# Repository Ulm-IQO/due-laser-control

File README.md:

# DUE laser control
A high resolution analog-digital digital-analog converter with PID to control
a Sirah Matisse ring laser for time resolved spectral scans.

## Hardware
An Arduino Due is used to control an AD7176 AD converter connected to 
a strain gauge measuring the laser reference cavity length and
an AD5791 DA converter that is used to drive the piezo amplifier for
the piezo that changes the reference cavity length.

We use the EVAL-AD7176-2SDZ and EVAL-AD5791SDZ reference boards with
a custom power supply (layout TBD).

A breakout board to adapt the existing RJ50 connector to SMA is also provided.

## Firmware
Right now, this can only be built with the Arduino IDE, but an addition to 
https://github.com/sudar/Arduino-Makefile is being worked on.

## Software
https://github.com/Ulm-IQO/qudi will be used to provide a user-friendly interface.

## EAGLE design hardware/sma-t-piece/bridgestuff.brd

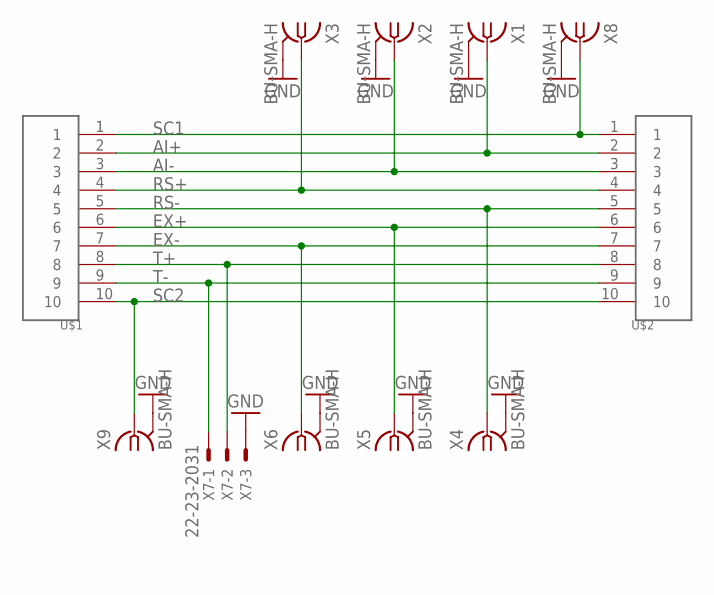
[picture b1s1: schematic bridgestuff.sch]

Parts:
U$1, U$2: RJ50-STEWARD; RJ50
X1, X2, X3, X4, X5, X6, X8, X9: BU-SMA-H
X7: 22-23-2031

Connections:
AI+: U$1.2, U$2.2, X1.1
AI-: U$1.3, U$2.3, X2.1
EX+: U$1.6, U$2.6, X5.1
EX-: U$1.7, U$2.7, X6.1
GND: X1.2, X1.3 (2), X1.4 (2), X1.5 (2), X2.2, X2.3 (2), X2.4 (2), X2.5 (2), X3.2, X3.3 (2), X3.4 (2), X3.5 (2), X4.2, X4.3 (2), X4.4 (2), X4.5 (2), X5.2, X5.3 (2), X5.4 (2), X5.5 (2), X6.2, X6.3 (2), X6.4 (2), X6.5 (2), X7.3, X8.2, X8.3 (2), X8.4 (2), X8.5 (2), X9.2, X9.3 (2), X9.4 (2), X9.5 (2)
RS+: U$1.4, U$2.4, X3.1
RS-: U$1.5, U$2.5, X4.1
SC1: U$1.1, U$2.1, X8.1
SC2: U$1.10, U$2.10, X9.1
T+: U$1.8, U$2.8, X7.2
T-: U$1.9, U$2.9, X7.1

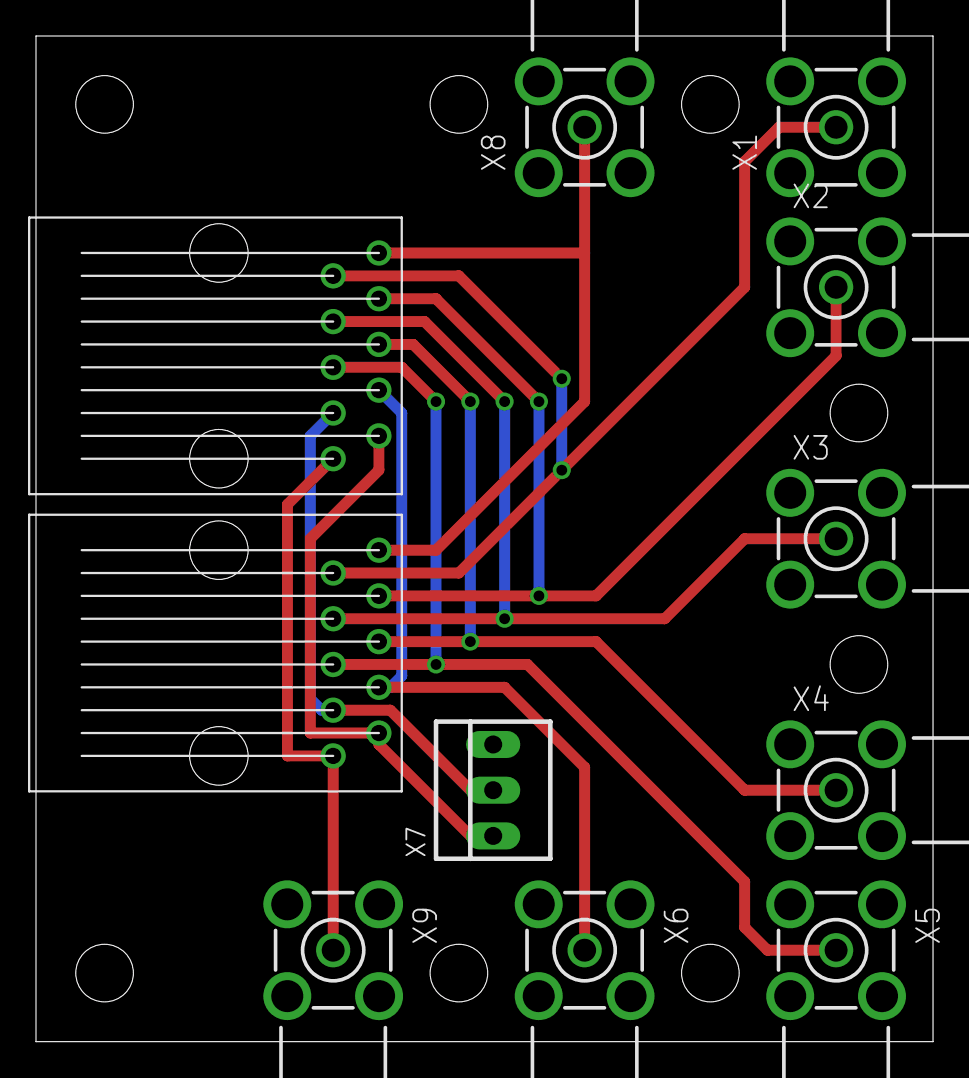
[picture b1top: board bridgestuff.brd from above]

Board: 2 copper layers, 49.8 x 55.9 mm, 11 parts (0 on the bottom side), 11 nets.

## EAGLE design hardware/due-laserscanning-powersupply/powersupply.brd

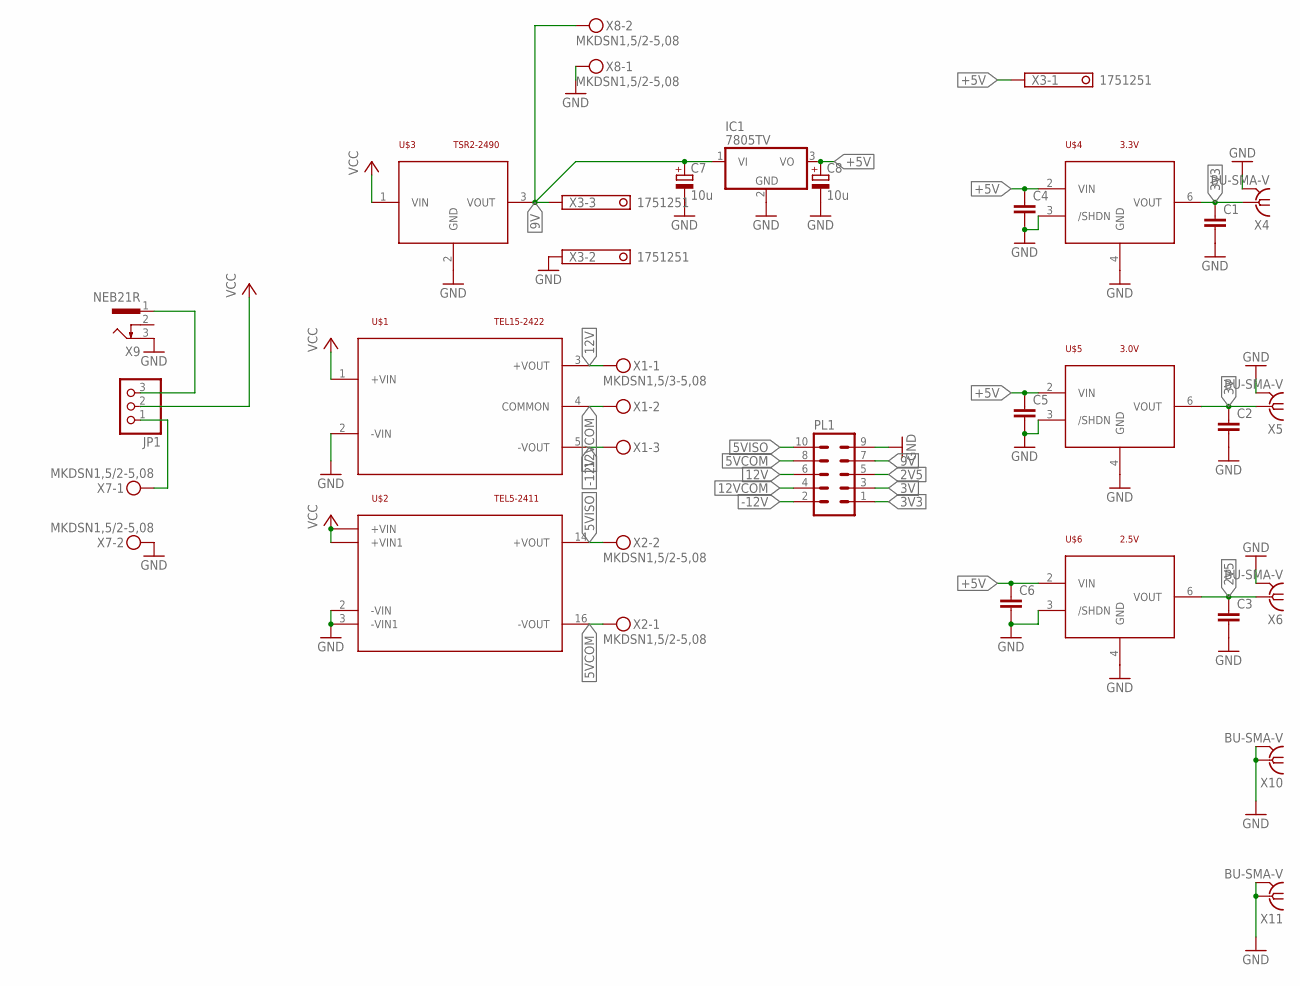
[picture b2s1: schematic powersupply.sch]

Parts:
C1, C2, C3, C4, C5, C6: C-EUC0805; C0805
C7, C8: 10u; PANASONIC_B
IC1: 7805TV; TO220V
JP1: PINHD-1X3; 1X03
PL1: 10V
U$1: TEL15-2422; TEL-15
U$2: TEL5-2411; TEL-5-SINGLE
U$3: TSR2-2490; TSR2
U$4: 3.3V; SO8
U$5: 3.0V; SO8
U$6: 2.5V; SO8
X1: MKDSN1,5/3-5,08
X2, X7, X8: MKDSN1,5/2-5,08
X3: 1751251
X4, X5, X6, X10, X11: BU-SMA-V
X9: NEB21R

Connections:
2V5: C3.1, PL1.5, U$6.6 (VOUT), X6.1
3V: C2.1, PL1.3, U$5.6 (VOUT), X5.1
3V3: C1.1, PL1.1, U$4.6 (VOUT), X4.1
5VCOM: PL1.8, U$2.16 (-VOUT), X2.1
5VISO: PL1.10, U$2.14 (+VOUT), X2.2
9V: C7.+, IC1.1 (VI), PL1.7, U$3.3 (VOUT), X3.3, X8.2
12V: PL1.6, U$1.3 (+VOUT), X1.1
12VCOM: PL1.4, U$1.4 (COMMON), X1.2
+5V: C4.1, C5.1, C6.1, C8.+, IC1.3 (VO), U$4.2 (VIN), U$5.2 (VIN), U$6.2 (VIN), X3.1
-12V: PL1.2, U$1.5 (-VOUT), X1.3
GND: C1.2, C2.2, C3.2, C4.2, C5.2, C6.2, C7.-, C8.-, IC1.2 (GND), PL1.9, U$1.2 (-VIN), U$2.2 (-VIN), U$2.3 (-VIN1), U$3.2 (GND), U$4.3 (/SHDN), U$4.4 (GND), U$5.3 (/SHDN), U$5.4 (GND), U$6.3 (/SHDN), U$6.4 (GND), X3.2, X4.2, X4.3 (2), X4.4 (2), X4.5 (2), X5.2, X5.3 (2), X5.4 (2), X5.5 (2), X6.2, X6.3 (2), X6.4 (2), X6.5 (2), X7.2, X8.1, X9.3, X10.1, X10.2, X10.3 (2), X10.4 (2), X10.5 (2), X11.1, X11.2, X11.3 (2), X11.4 (2), X11.5 (2)
unnamed: JP1.1, X7.1
unnamed: JP1.3, X9.1
VCC: JP1.2, U$1.1 (+VIN), U$2.22 (+VIN), U$2.23 (+VIN1), U$3.1 (VIN)

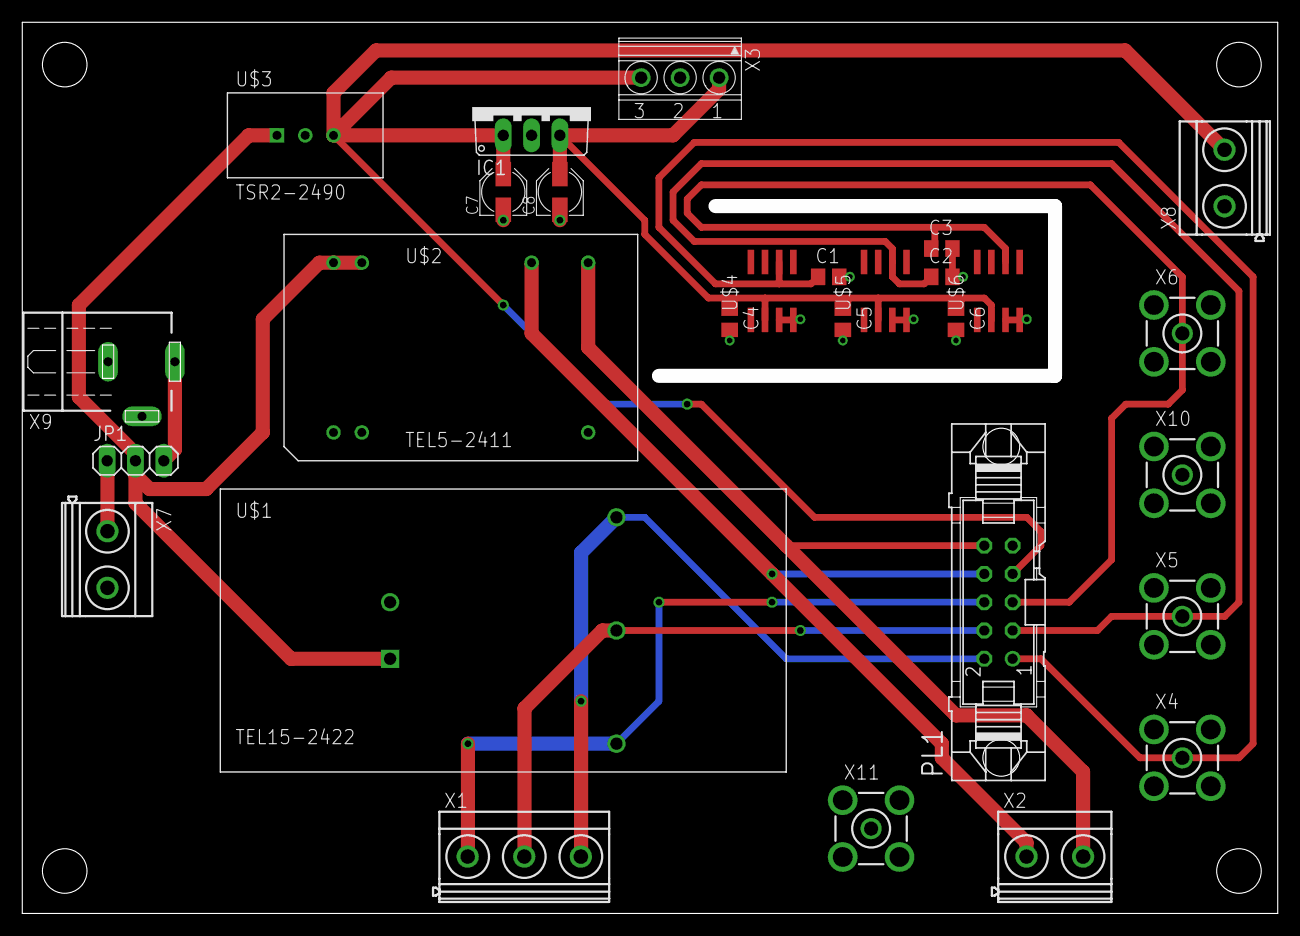
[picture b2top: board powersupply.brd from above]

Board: 2 copper layers, 111.4 x 78.7 mm, 28 parts (0 on the bottom side), 14 nets.

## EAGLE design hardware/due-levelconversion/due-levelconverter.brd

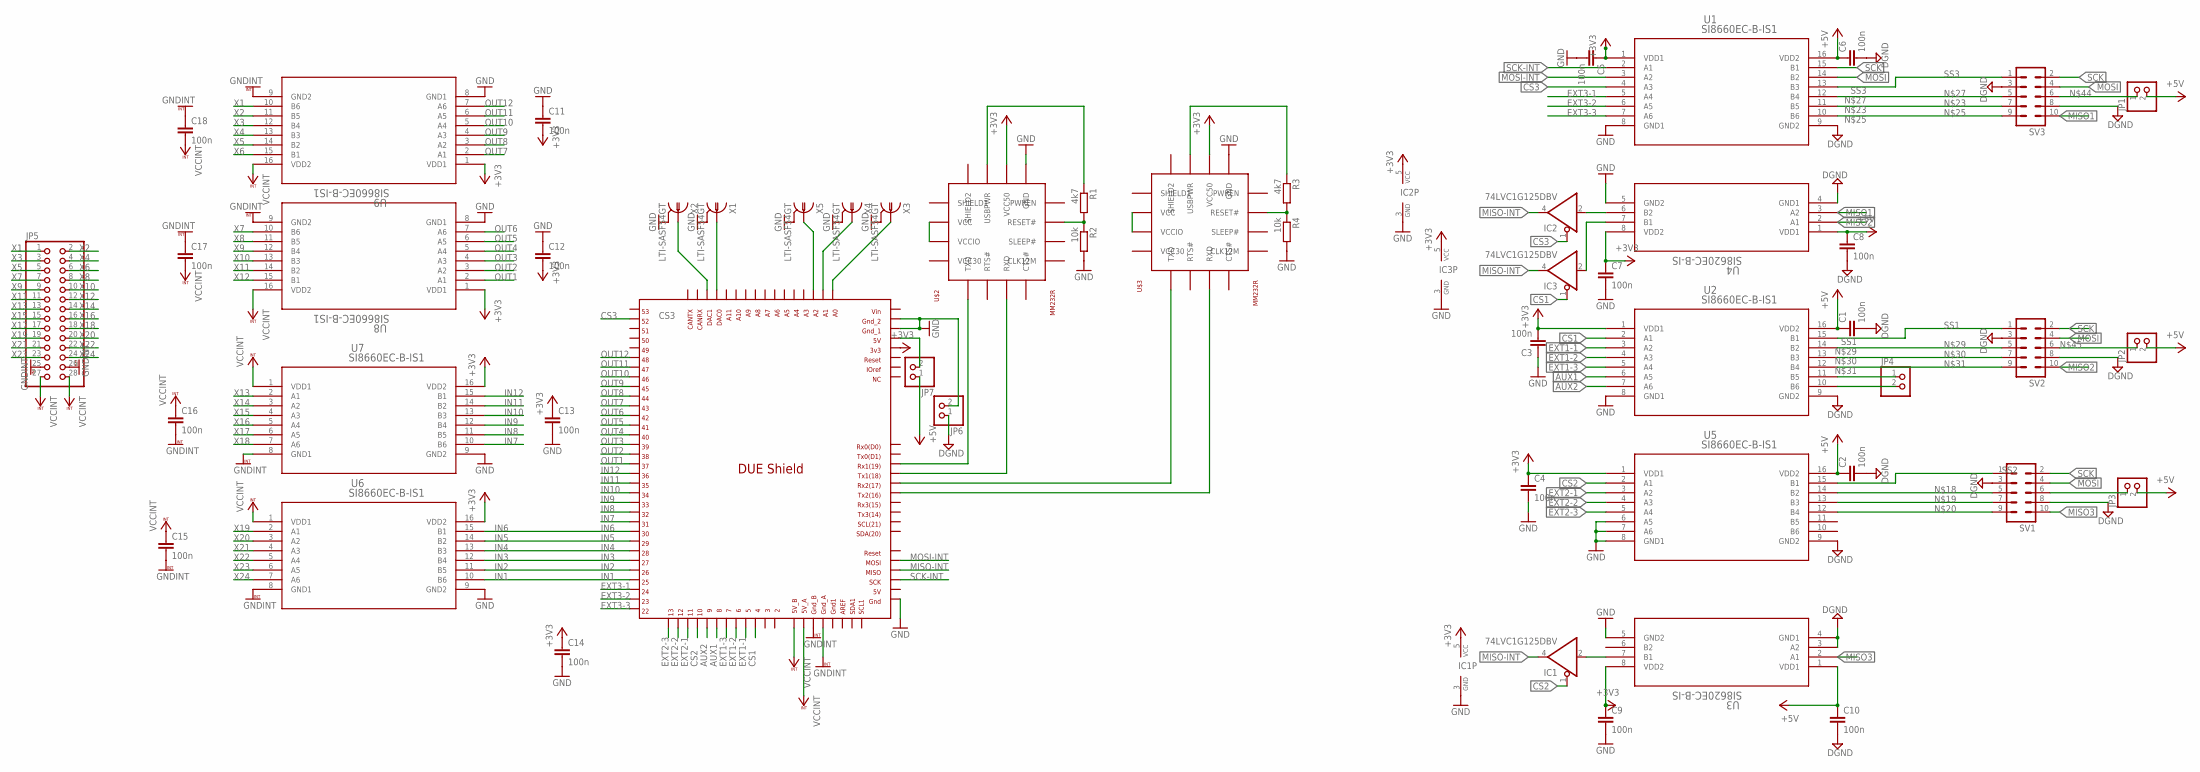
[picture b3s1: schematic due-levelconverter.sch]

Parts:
C1, C2, C3, C4, C5, C6, C7, C8, C9, C10, C11, C12, C13, C14, C15, C16, C17, C18: 100n; C0805
IC1, IC2, IC3: 74LVC1G125DBV; SOT23-5
JP1, JP2, JP3, JP4, JP6, JP7: PINHD-1X2; 1X02
JP5: PINHD-2X14; 2X14
R1, R3: 4k7; R0805
R2, R4: 10k; R0805
SV1, SV2, SV3: ML10
U1, U2, U5, U6, U7, U8, U9: SI8660EC-B-IS1; SOIC-16
U3, U4: SI8620EC-B-IS; SOIC-8
U$1: DUE(NORMAL)
U$2, U$3: MM232R
X1, X2, X3, X4, X5: LTI-SASF54GT

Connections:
+3V3: C3.2, C4.1, C5.1, C7.1, C9.1, C11.2, C12.2, C13.1, C14.1, IC1.5 (VCC), IC2.5 (VCC), IC3.5 (VCC), U1.1 (VDD1), U2.1 (VDD1), U3.8 (VDD2), U4.8 (VDD2), U5.1 (VDD1), U6.16 (VDD2), U7.16 (VDD2), U8.1 (VDD1), U9.1 (VDD1), U$1.3V3, U$2.P$14 (VCC50), U$3.P$14 (VCC50)
+5V: C1.1, C2.1, C6.1, C8.1, C10.1, JP1.2, JP2.2, JP3.2, JP7.1, U1.16 (VDD2), U2.16 (VDD2), U3.1 (VDD1), U4.1 (VDD1), U5.16 (VDD2)
AUX1: U2.6 (A5), U$1.8
AUX2: U2.7 (A6), U$1.9
CS1: IC3.1 (OE), U2.2 (A1), U$1.4
CS2: IC1.1 (OE), U5.2 (A1), U$1.10
CS3: IC2.1 (OE), U1.4 (A3), U$1.52
DGND: C1.2, C2.2, C6.2, C8.2, C10.2, JP6.1, SV1.3, SV1.8, SV2.3, SV2.8, SV3.3, SV3.8, U1.9 (GND2), U2.9 (GND2), U3.3 (A2), U3.4 (GND1), U4.4 (GND1), U5.9 (GND2)
EXT1-1: U2.3 (A2), U$1.5
EXT1-2: U2.4 (A3), U$1.6
EXT1-3: U2.5 (A4), U$1.7
EXT2-1: U5.3 (A2), U$1.11
EXT2-2: U5.4 (A3), U$1.12
EXT2-3: U5.5 (A4), U$1.13
EXT3-1: U1.5 (A4), U$1.24
EXT3-2: U1.6 (A5), U$1.23
EXT3-3: U1.7 (A6), U$1.22
GND: C3.1, C4.2, C5.2, C7.2, C9.2, C11.1, C12.1, C13.2, C14.2, IC1.3 (GND), IC2.3 (GND), IC3.3 (GND), JP6.2, R2.2, R4.2, U1.8 (GND1), U2.8 (GND1), U3.5 (GND2), U4.5 (GND2), U5.6 (A5), U5.7 (A6), U5.8 (GND1), U6.9 (GND2), U7.9 (GND2), U8.8 (GND1), U9.8 (GND1), U$1.5V_ICSP, U$1.GND_1, U$1.GND_2, U$2.P$13 (GND), U$3.P$13 (GND), X1.2, X1.3 (2), X1.4 (2), X1.5 (2), X2.2, X2.3 (2), X2.4 (2), X2.5 (2), X3.2, X3.3 (2), X3.4 (2), X3.5 (2), X4.2, X4.3 (2), X4.4 (2), X4.5 (2), X5.2, X5.3 (2), X5.4 (2), X5.5 (2)
GNDINT: C15.2, C16.2, C17.1, C18.1, JP5.25, JP5.26, U6.8 (GND1), U7.8 (GND1), U8.9 (GND2), U9.9 (GND2), U$1.GND_A, U$1.GND_B
IN1: U6.10 (B6), U$1.25
IN2: U6.11 (B5), U$1.26
IN3: U6.12 (B4), U$1.27
IN4: U6.13 (B3), U$1.28
IN5: U6.14 (B2), U$1.29
IN6: U6.15 (B1), U$1.30
IN7: U7.10 (B6), U$1.31
IN8: U7.11 (B5), U$1.32
IN9: U7.12 (B4), U$1.33
IN10: U7.13 (B3), U$1.34
IN11: U7.14 (B2), U$1.35
IN12: U7.15 (B1), U$1.36
MISO1: SV3.10, U4.3 (A2)
MISO2: SV2.10, U4.2 (A1)
MISO3: SV1.10, U3.2 (A1)
MISO-INT: IC1.4 (O), IC2.4 (O), IC3.4 (O), U$1.MISO_ICSP
MOSI: SV1.4, SV2.4, SV3.4, U1.14 (B2)
MOSI-INT: U1.3 (A2), U$1.MOSI_ICSP
unnamed: JP7.2, U$1.5V
unnamed: IC1.2 (I), U3.7 (B1)
unnamed: U$1.DAC0, X1.1
unnamed: U$1.DAC1, X2.1
unnamed: U$1.A0, X3.1
unnamed: U$1.A1, X4.1
unnamed: U$1.A2, X5.1
unnamed: U$3.P$2 (VCC), U$3.P$3 (VCCIO)
unnamed: IC2.2 (I), U4.6 (B2)
unnamed: U$2.P$2 (VCC), U$2.P$3 (VCCIO)
unnamed: SV1.5, U5.14 (B2)
unnamed: SV1.7, U5.13 (B3)
unnamed: SV1.9, U5.12 (B4)
unnamed: IC3.2 (I), U4.7 (B1)
unnamed: SV3.7, U1.11 (B5)
unnamed: SV3.9, U1.10 (B6)
unnamed: SV3.5, U1.12 (B4)
unnamed: SV2.5, U2.14 (B2)
unnamed: SV2.7, U2.13 (B3)
unnamed: SV2.9, U2.12 (B4)
unnamed: U$1.RX1, U$2.P$5 (TXD)
unnamed: U$1.TX1, U$2.P$7 (RXD)
unnamed: U$1.RX2, U$3.P$5 (TXD)
unnamed: U$1.TX2, U$3.P$7 (RXD)
unnamed: R1.2, R2.1, U$2.P$11 (RESET#)
unnamed: R3.2, R4.1, U$3.P$11 (RESET#)
unnamed: R1.1, U$2.P$15 (USBPWR)
unnamed: R3.1, U$3.P$15 (USBPWR)
unnamed: JP1.1, SV3.6
unnamed: JP2.1, SV2.6
unnamed: JP3.1, SV1.6
unnamed: JP4.1, U2.11 (B5)
unnamed: JP4.2, U2.10 (B6)
OUT1: U8.2 (A1), U$1.37
OUT2: U8.3 (A2), U$1.38
OUT3: U8.4 (A3), U$1.39
OUT4: U8.5 (A4), U$1.40
OUT5: U8.6 (A5), U$1.41
OUT6: U8.7 (A6), U$1.42
OUT7: U9.2 (A1), U$1.43
OUT8: U9.3 (A2), U$1.44
OUT9: U9.4 (A3), U$1.45
OUT10: U9.5 (A4), U$1.46
OUT11: U9.6 (A5), U$1.47
OUT12: U9.7 (A6), U$1.48
SCK: SV1.2, SV2.2, SV3.2, U1.15 (B1)
SCK-INT: U1.2 (A1), U$1.SCK_ICSP
SS1: SV2.1, U2.15 (B1)
SS2: SV1.1, U5.15 (B1)
SS3: SV3.1, U1.13 (B3)
VCCINT: C15.1, C16.1, C17.2, C18.2, JP5.27, JP5.28, U6.1 (VDD1), U7.1 (VDD1), U8.16 (VDD2), U9.16 (VDD2), U$1.5V_A, U$1.5V_B
X1: JP5.1, U9.10 (B6)
X2: JP5.2, U9.11 (B5)
X3: JP5.3, U9.12 (B4)
X4: JP5.4, U9.13 (B3)
X5: JP5.5, U9.14 (B2)
X6: JP5.6, U9.15 (B1)
X7: JP5.7, U8.10 (B6)
X8: JP5.8, U8.11 (B5)
X9: JP5.9, U8.12 (B4)
X10: JP5.10, U8.13 (B3)
X11: JP5.11, U8.14 (B2)
X12: JP5.12, U8.15 (B1)
X13: JP5.13, U7.2 (A1)
X14: JP5.14, U7.3 (A2)
X15: JP5.15, U7.4 (A3)
X16: JP5.16, U7.5 (A4)
X17: JP5.17, U7.6 (A5)
X18: JP5.18, U7.7 (A6)
X19: JP5.19, U6.2 (A1)
X20: JP5.20, U6.3 (A2)
X21: JP5.21, U6.4 (A3)
X22: JP5.22, U6.5 (A4)
X23: JP5.23, U6.6 (A5)
X24: JP5.24, U6.7 (A6)

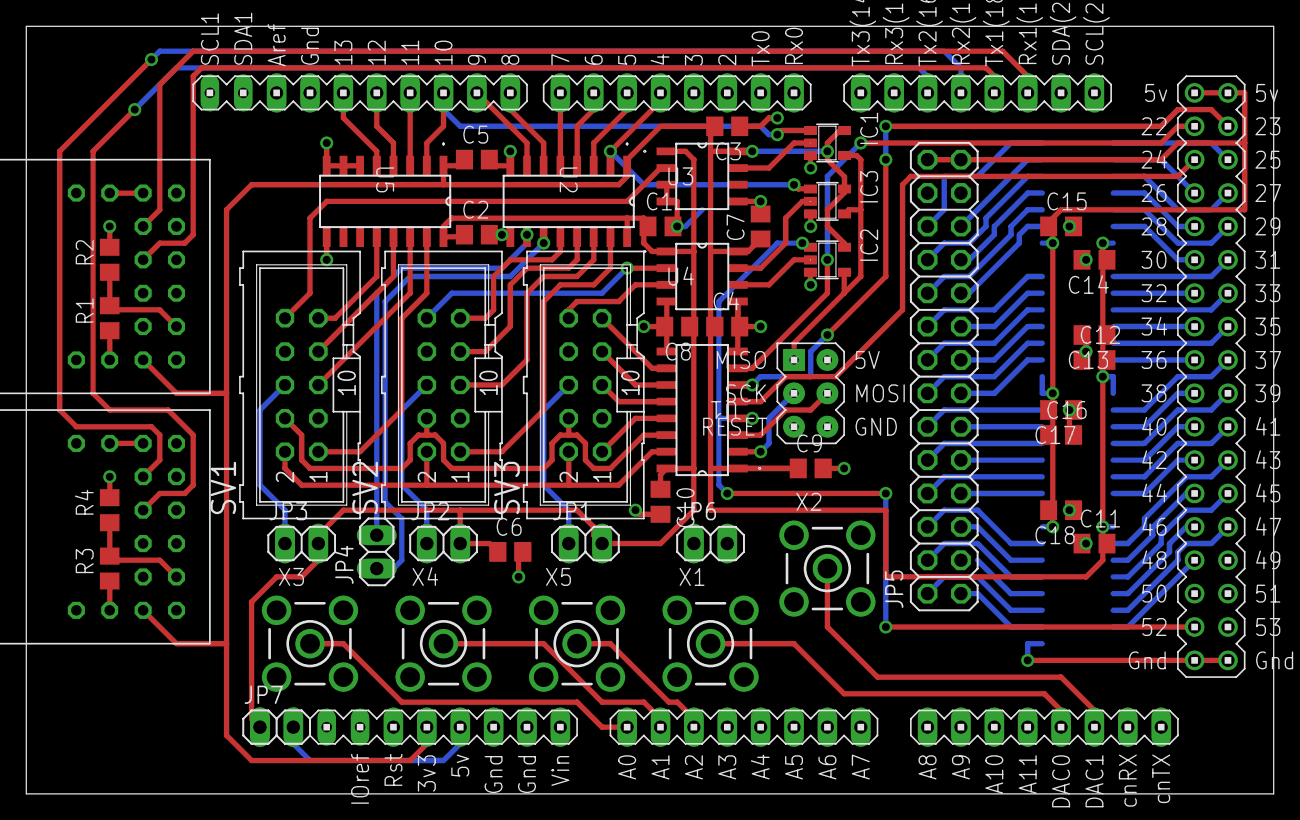
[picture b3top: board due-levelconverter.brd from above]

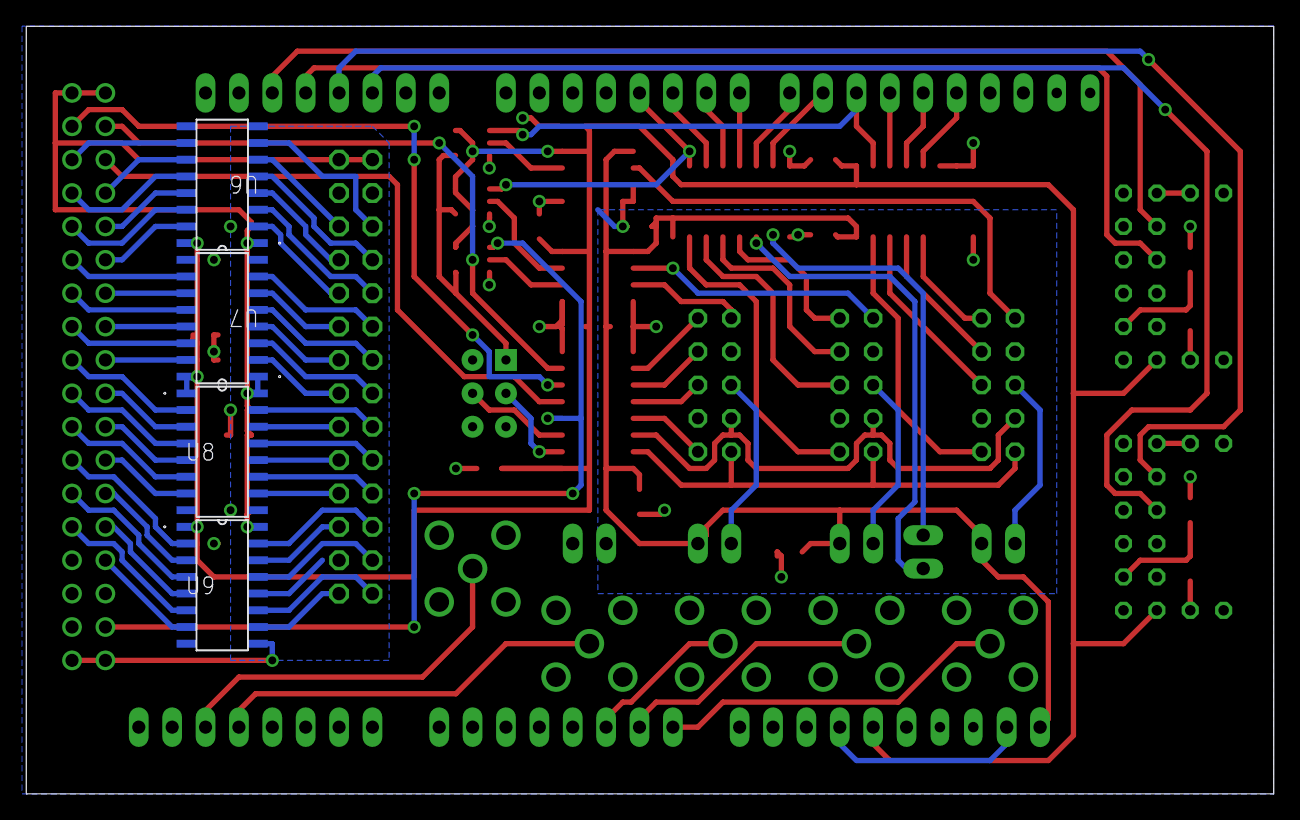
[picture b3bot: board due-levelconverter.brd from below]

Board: 2 copper layers, 94.9 x 58.4 mm, 52 parts (4 on the bottom side), 112 nets.

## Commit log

2016-07-12 initial project commit
2016-07-12 Create README.md
    describe components a bit
2016-07-17 add function definition before usage (not necessary in all arduino versions, but definitely in C)
2016-07-19 add first revision of powersupply board
2016-07-19 update arduino makefile
2016-07-19 split firmware source into multiple files
2016-07-23 make boardsetup work
2016-07-23 update powersupply board
2016-07-23 ignore most of the non-source files
2016-08-09 first revision of powersupply board was a total failure due to small holes and mirrored components
2016-09-09 initalisation parameters for 7176
2016-12-26 finding a measurement scheme that works
2016-12-28 add labels to pcb
2017-01-03 Correct the serial receiver code so it does not swallow letters anymore.
2017-01-03 Add slightly modified SCPI parser from https://github.com/LachlanGunn/oic to repository.
2017-07-25 data print control
2017-07-28 more commands
